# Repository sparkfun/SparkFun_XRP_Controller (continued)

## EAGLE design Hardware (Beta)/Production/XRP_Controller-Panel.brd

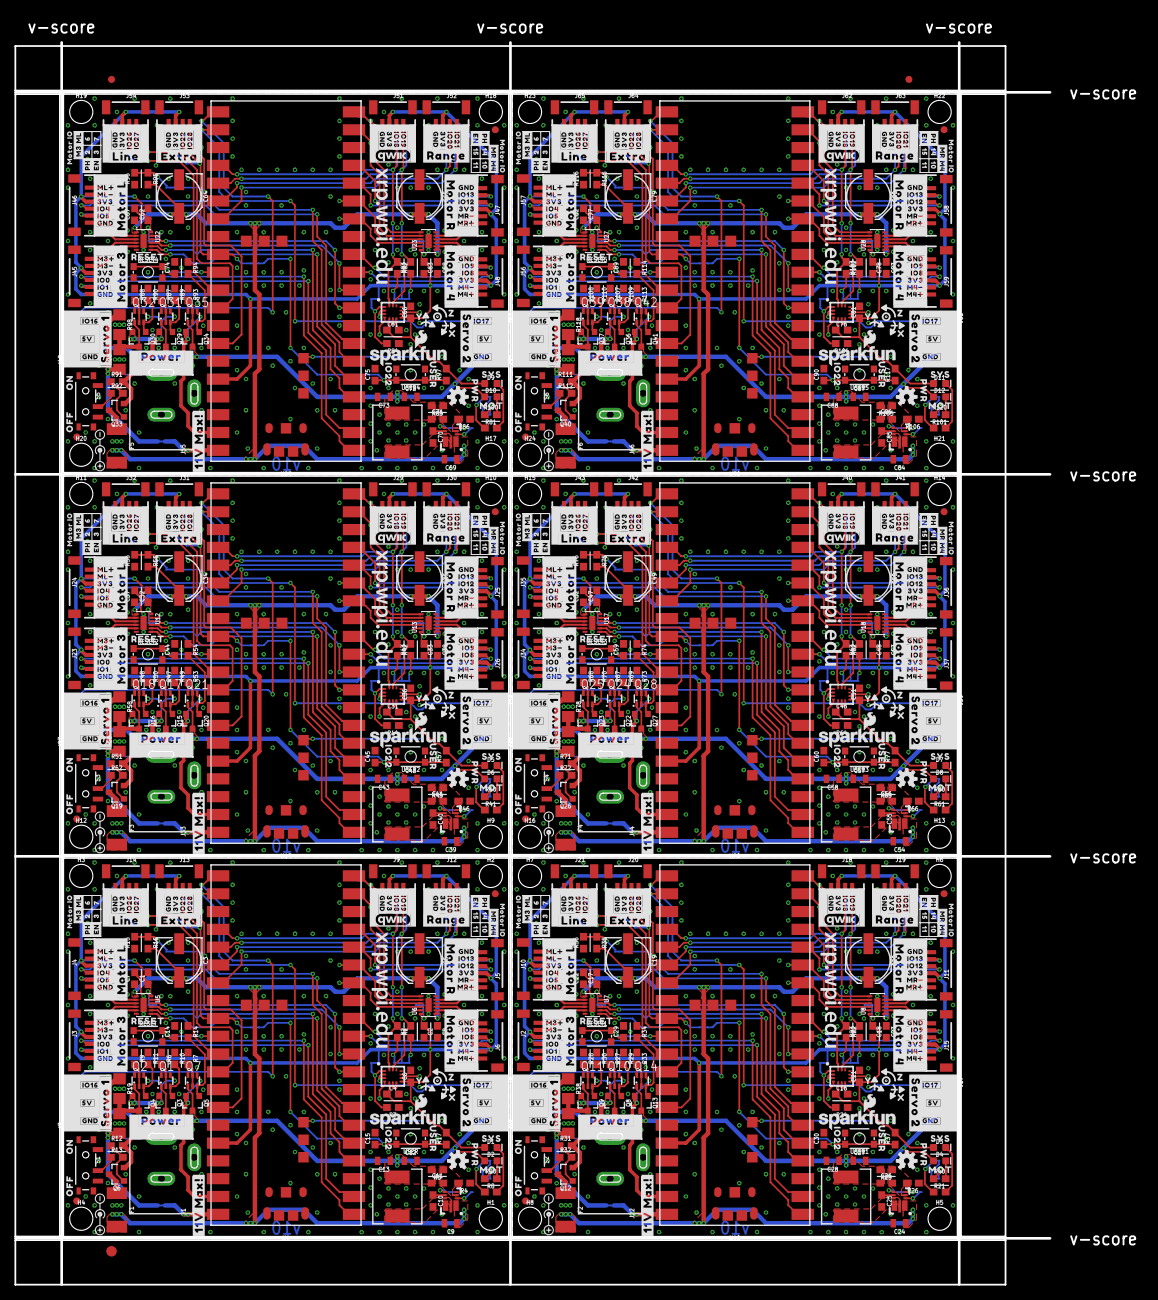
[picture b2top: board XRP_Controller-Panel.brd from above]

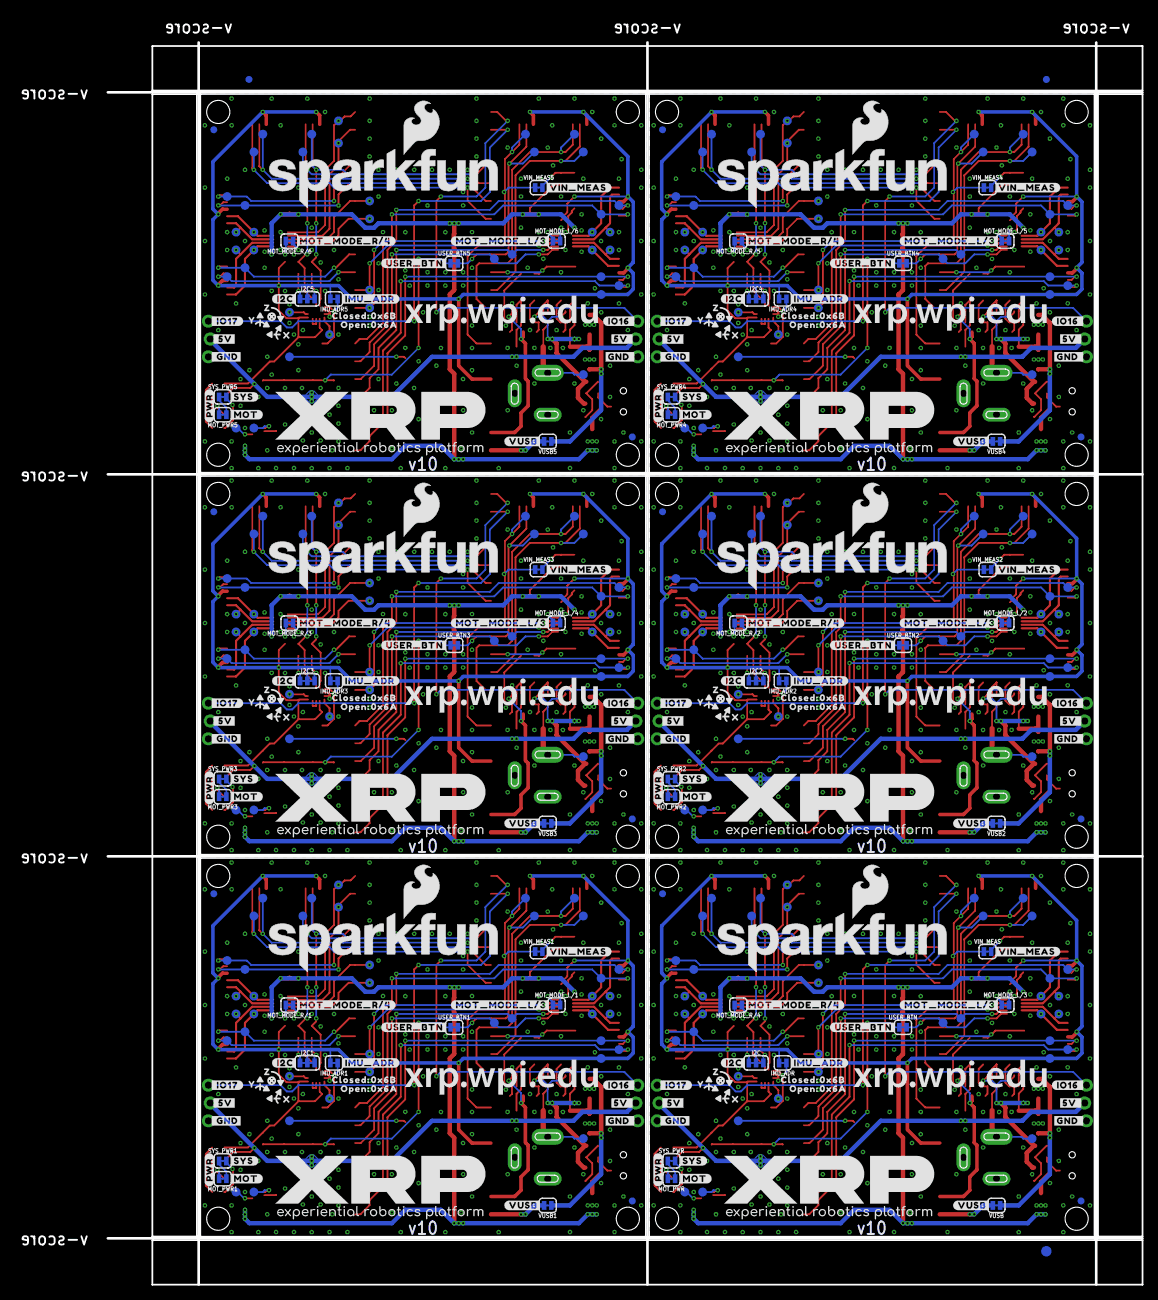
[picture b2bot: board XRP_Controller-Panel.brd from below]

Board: 2 copper layers, 147.6 x 177.2 mm, 1434 parts (459 on the bottom side), 438 nets.

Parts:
C1, C2, C4, C6, C7, C8, C10, C14, C15, C16, C17, C18, C21, C22, C23, C25, C29, C30, C31, C32, C33, C36, C37, C38, C40, C44, C45, C46, C47, C48, C51, C52, C53, C55, C59, C60, C61, C62, C63, C66, C67, C68, C70, C74, C75, C76, C77, C78, C81, C82, C83, C85, C89, C90: 0.1uF; 0603
C3, C5, C19, C20, C34, C35, C49, C50, C64, C65, C79, C80: 100uF; PANASONIC_D
C9, C24, C39, C54, C69, C84: 10uF; 0805
C11, C26, C41, C56, C71, C86: 47pF; 0603
C12, C13, C27, C28, C42, C43, C57, C58, C72, C73, C87, C88: 22uF; 0805
D1, D2, D3, D4, D5, D6, D7, D8, D9, D10, D11, D12: Red; LED-0603
E$1, E$2, E$3, E$4: FIDUCIAL-1X2
E$5, E$6: FIDUCIAL-1.5X3
F1, F2, F3, F4, F5, F6: 16V/2.5A(5A TRIP); 1812
FD1, FD2, FD3, FD4, FD5, FD6, FD7, FD8, FD9, FD10, FD11, FD12, FD13, FD14, FD15, FD16, FD17, FD18, FD19, FD20, FD21, FD22, FD23, FD24: FIDUCIAL1X2; FIDUCIAL-1X2
H1, H2, H3, H4, H5, H6, H7, H8, H9, H10, H11, H12, H13, H14, H15, H16, H17, H18, H19, H20, H21, H22, H23, H24: STAND-OFF
I2C, I2C1, I2C2, I2C3, I2C4, I2C5: JUMPER-SMT_3_2-NC_TRACE_SILK; SMT-JUMPER_3_2-NC_TRACE_SILK
IMU_ADR, IMU_ADR1, IMU_ADR2, IMU_ADR3, IMU_ADR4, IMU_ADR5: JUMPER-SMT_2_NC_TRACE_SILK; SMT-JUMPER_2_NC_TRACE_SILK
J1, J22, J33, J44, J55, J66: POWER_JACKPOWER_JACK_SLOT; POWER_JACK_PTH_SLOT
J2, J3, J4, J5, J6, J10, J11, J15, J23, J24, J25, J26, J34, J35, J36, J37, J45, J46, J47, J48, J56, J57, J58, J59: JST_6_PIN_VERTICAL; JST-6-SMD-VERT-1.0MM
J7, J8, J16, J17, J27, J28, J38, J39, J49, J50, J60, J61: 1X03_LOCK_NO_SILK
J9, J12, J13, J14, J18, J19, J20, J21, J29, J30, J31, J32, J40, J41, J42, J43, J51, J52, J53, J54, J62, J63, J64, J65: Vertical Qwiic Connector; JST04_1MM_VERT
L1, L2, L3, L4, L5, L6: 6.8UH; 07A7_6U8H
LOGO1, LOGO2, LOGO7, LOGO10, LOGO13, LOGO16: OSHW-LOGOS; OSHW-LOGO-S
LOGO3, LOGO5, LOGO8, LOGO11, LOGO14, LOGO17: SFE_LOGO_NAME_FLAME.3_INCH; SFE_LOGO_NAME_FLAME_.3
LOGO4, LOGO6, LOGO9, LOGO12, LOGO15, LOGO18: SFE_LOGO_NAME_FLAME.1_INCH; SFE_LOGO_NAME_FLAME_.1
MOT_MODE_L/1, MOT_MODE_L/2, MOT_MODE_L/3, MOT_MODE_L/4, MOT_MODE_L/5, MOT_MODE_L/6: JUMPER-SMT_2_NC_TRACE_SILK; SMT-JUMPER_2_NC_TRACE_SILK
MOT_MODE_R/1, MOT_MODE_R/2, MOT_MODE_R/3, MOT_MODE_R/4, MOT_MODE_R/5, MOT_MODE_R/6: JUMPER-SMT_2_NC_TRACE_SILK; SMT-JUMPER_2_NC_TRACE_SILK
MOT_PWR, MOT_PWR1, MOT_PWR2, MOT_PWR3, MOT_PWR4, MOT_PWR5: JUMPER-SMT_2_NC_TRACE_SILK; SMT-JUMPER_2_NC_TRACE_SILK
Q1, Q2, Q7, Q10, Q11, Q14, Q17, Q18, Q21, Q24, Q25, Q28, Q31, Q32, Q35, Q38, Q39, Q42: SOT363_PHILIPS
Q3, Q4, Q5, Q6, Q8, Q9, Q12, Q13, Q15, Q16, Q19, Q20, Q22, Q23, Q26, Q27, Q29, Q30, Q33, Q34, Q36, Q37, Q40, Q41: 20V/4.2A/52mΩ/1.4W; SOT23-3
R1, R2, R22, R23, R42, R43, R62, R63, R82, R83, R102, R103: 2.2k; 0603
R3, R6, R7, R9, R12, R13, R16, R17, R24, R27, R28, R31, R32, R33, R35, R37, R44, R47, R48, R51, R52, R53, R55, R57, R64, R67, R68, R71, R72, R73, R75, R77, R84, R87, R88, R91, R92, R93, R95, R97, R104, R107, R108, R111, R112, R113, R115, R117: 100k; 0603
R4, R15, R26, R36, R46, R56, R66, R76, R86, R96, R106, R116: 33k; 0603
R5, R25, R45, R65, R85, R105: 180k; 0603
R8, R21, R41, R61, R81, R101: 4.7k; 0603
R10, R11, R14, R29, R30, R34, R49, R50, R54, R69, R70, R74, R89, R90, R94, R109, R110, R114: 1M; 0603
R18, R19, R38, R39, R58, R59, R78, R79, R98, R99, R118, R119: 10; 1206
R20, R40, R60, R80, R100, R120: 10k; 0603
RESET, RESET1, RESET2, RESET3, RESET4, RESET5: MOMENTARY-SWITCH-SPST-SMD-4.6X2.8MM; TACTILE_SWITCH_SMD_4.6X2.8MM
S1, S2, S3, S4, S5, S6: SWITCH_SPST_SMD_A
SYS_PWR, SYS_PWR1, SYS_PWR2, SYS_PWR3, SYS_PWR4, SYS_PWR5: JUMPER-SMT_2_NC_TRACE_SILK; SMT-JUMPER_2_NC_TRACE_SILK
TP1, TP2, TP3, TP4, TP5, TP6, TP7, TP8, TP9, TP10, TP11, TP12, TP13, TP14, TP15, TP16, TP17, TP18, TP19, TP20, TP21, TP22, TP23, TP24, TP25, TP26, TP27, TP28, TP29, TP30, TP31, TP32, TP33, TP34, TP35, TP36, TP37, TP38, TP39, TP40, TP41, TP42, TP43, TP44, TP45, TP46, TP47, TP48, TP49, TP50, TP51, TP52, TP53, TP54, TP55, TP56, TP57, TP58, TP59, TP60, TP61, TP62, TP63, TP64, TP65, TP66, TP67, TP68, TP69, TP70, TP71, TP72, TP73, TP74, TP75, TP76, TP77, TP78, TP79, TP80, TP81, TP82, TP83, TP84, TP85, TP86, TP87, TP88, TP89, TP90, TP91, TP92, TP93, TP94, TP95, TP96, TP97, TP98, TP99, TP100, TP101, TP102, TP103, TP104, TP105, TP106, TP107, TP108, TP109, TP110, TP111, TP112, TP113, TP114, TP115, TP116, TP117, TP118, TP119, TP120, TP121, TP122, TP123, TP124, TP125, TP126, TP127, TP128, TP129, TP130, TP131, TP132, TP133, TP134, TP135, TP136, TP137, TP138, TP139, TP140, TP141, TP142, TP143, TP144, TP145, TP146, TP147, TP148, TP149, TP150, TP151, TP152, TP153, TP154, TP155, TP156, TP157, TP158, TP159, TP160, TP161, TP162, TP163, TP164, TP165, TP166, TP167, TP168, TP169, TP170, TP171, TP172, TP173, TP174, TP175, TP176, TP177, TP178, TP179, TP180, TP181, TP182, TP183, TP184, TP185, TP186, TP187, TP188, TP189, TP190, TP191, TP192, TP193, TP194, TP195, TP196, TP197, TP198, TP199, TP200, TP201, TP202, TP203, TP204, TP205, TP206, TP207, TP208, TP209, TP210, TP211, TP212, TP213, TP214, TP215, TP216, TP217, TP218, TP219, TP220, TP221, TP222, TP223, TP224, TP225, TP226, TP227, TP228, TP229, TP230, TP231, TP232, TP233, TP234: TEST-POINT3X5; PAD.03X.05
U1, U10, U15, U20, U25, U30: RPI_PICO_W_XRP; RPI_PICO_W
U2, U9, U14, U19, U24, U29: AP63357; V-DFN3020-13
U3, U4, U11, U16, U21, U26: LSM6DS0X; LGA14L
U5, U6, U7, U8, U12, U13, U17, U18, U22, U23, U27, U28: DRV8835; WSON-12
U$1, U$165, U$279, U$393, U$507, U$621: #MOTOR_3#0
U$2, U$169, U$283, U$397, U$511, U$625: #SERVO_2#0
U$3, U$170, U$284, U$398, U$512, U$626: #11V_MAX###0
U$4, U$24, U$50, U$52, U$54, U$118, U$124, U$146, U$148, U$150, U$232, U$238, U$260, U$262, U$264, U$346, U$352, U$374, U$376, U$378, U$460, U$466, U$488, U$490, U$492, U$574, U$580, U$602, U$604, U$606: #GND#0
U$5, U$36, U$229, U$343, U$457, U$571: #POWER#0
U$6, U$112, U$230, U$344, U$458, U$572: PWR0
U$7, U$113, U$231, U$345, U$459, U$573: RESET0
U$8, U$167, U$281, U$395, U$509, U$623: #MOTOR_R#0
U$9, U$207, U$321, U$435, U$549, U$663: #MR##0
U$10, U$164, U$278, U$392, U$506, U$620: #MOTOR_L#0
U$11, U$166, U$280, U$394, U$508, U$622: #SERVO_1#0
U$12, U$168, U$282, U$396, U$510, U$624: #MOTOR_4#0
U$13, U$182, U$296, U$410, U$524, U$638: #VIN_MEAS#0
U$14, U$208, U$322, U$436, U$550, U$664: #MR##1
U$15, U$25, U$51, U$53, U$119, U$125, U$147, U$149, U$233, U$239, U$261, U$263, U$347, U$353, U$375, U$377, U$461, U$467, U$489, U$491, U$575, U$581, U$603, U$605: #3V3#0
U$16, U$205, U$319, U$433, U$547, U$661: #ML##0
U$17, U$33, U$41, U$43, U$129, U$131, U$137, U$139, U$243, U$245, U$251, U$253, U$357, U$359, U$365, U$367, U$471, U$473, U$479, U$481, U$585, U$587, U$593, U$595: #3V3#4
U$18, U$209, U$323, U$437, U$551, U$665: #M4##0
U$19, U$210, U$324, U$438, U$552, U$666: #M4##5
U$20, U$120, U$234, U$348, U$462, U$576: #IO0#0
U$21, U$121, U$235, U$349, U$463, U$577: #IO1#0
U$22, U$122, U$236, U$350, U$464, U$578: #IO5#0
U$23, U$123, U$237, U$351, U$465, U$579: #IO4#0
U$26, U$172, U$286, U$400, U$514, U$628: #GND_#0
U$27, U$171, U$285, U$399, U$513, U$627: #5V_#0
U$28, U$126, U$240, U$354, U$468, U$582: #IO8#0
U$29, U$127, U$241, U$355, U$469, U$583: #IO9#0
U$30, U$31, U$40, U$42, U$57, U$128, U$130, U$136, U$138, U$153, U$242, U$244, U$250, U$252, U$267, U$356, U$358, U$364, U$366, U$381, U$470, U$472, U$478, U$480, U$495, U$584, U$586, U$592, U$594, U$609: #GND#10
U$32, U$206, U$320, U$434, U$548, U$662: #ML##1
U$34, U$132, U$246, U$360, U$474, U$588: #IO12#0
U$35, U$133, U$247, U$361, U$475, U$589: #IO13#0
U$37, U$117, U$218, U$222, U$332, U$336, U$446, U$450, U$560, U$564, U$674, U$678: #PH#0
U$38, U$134, U$248, U$362, U$476, U$590: #IO27#0
U$39, U$135, U$249, U$363, U$477, U$591: #IO28#0
U$44, U$140, U$254, U$368, U$482, U$596: #IO26#0
U$45, U$141, U$255, U$369, U$483, U$597: #IO22#0
U$46, U$142, U$256, U$370, U$484, U$598: #IO18#0
U$47, U$143, U$257, U$371, U$485, U$599: #IO19#0
U$48, U$144, U$258, U$372, U$486, U$600: #IO20#0
U$49, U$145, U$259, U$373, U$487, U$601: #IO21#0
U$55, U$151, U$265, U$379, U$493, U$607: #5V#0
U$56, U$152, U$266, U$380, U$494, U$608: #IO16#0
U$58, U$154, U$268, U$382, U$496, U$610: #IO17#0
U$59, U$155, U$269, U$383, U$497, U$611: #5V#18
U$60, U$156, U$270, U$384, U$498, U$612: #I2C#0
U$61, U$173, U$287, U$401, U$515, U$629: #IO16_#0
U$62, U$157, U$271, U$385, U$499, U$613: ON0
U$63, U$158, U$272, U$386, U$500, U$614: OFF0
U$64, U$162, U$276, U$390, U$504, U$618: #IMU_ADR#0
U$65, U$116, U$217, U$221, U$331, U$335, U$445, U$449, U$559, U$563, U$673, U$677: #EN#0
U$66, U$194, U$308, U$422, U$536, U$650: #MOT_MODE_L#3#0
U$67, U$195, U$309, U$423, U$537, U$651: SYS0
U$68, U$191, U$305, U$419, U$533, U$647: IO220
U$69, U$192, U$306, U$420, U$534, U$648: #RANGE#0
U$70, U$193, U$307, U$421, U$535, U$649: #MOT_MODE_R#4#0
U$71, U$196, U$310, U$424, U$538, U$652: MOT0
U$72, U$201, U$315, U$429, U$543, U$657: XRP_URL_3MM
U$73, U$199, U$313, U$427, U$541, U$655: #PWR#0
U$74, U$163, U$277, U$391, U$505, U$619: #LINE#0
U$75, U$174, U$288, U$402, U$516, U$630: #_GND#0
U$76, U$175, U$289, U$403, U$517, U$631: #_5V#0
U$77, U$176, U$290, U$404, U$518, U$632: #_IO17#0
U$78, U$177, U$291, U$405, U$519, U$633: POLARITY_MARKING_CENTER_POSITIVE#JPG
U$79, U$88, U$159, U$178, U$273, U$292, U$387, U$406, U$501, U$520, U$615, U$634: X0
U$80, U$89, U$160, U$179, U$274, U$293, U$388, U$407, U$502, U$521, U$616, U$635: Y0
U$81, U$90, U$161, U$180, U$275, U$294, U$389, U$408, U$503, U$522, U$617, U$636: Z0
U$82, U$181, U$295, U$409, U$523, U$637: #EXTRA#0
U$83, U$183, U$297, U$411, U$525, U$639: USER0
U$84, U$184, U$298, U$412, U$526, U$640: #USER_BTN#0
U$85, U$185, U$299, U$413, U$527, U$641: 0X6B0
U$86, U$186, U$300, U$414, U$528, U$642: 0X6A0
U$87, U$187, U$301, U$415, U$529, U$643: OPEN#0
U$91, U$188, U$302, U$416, U$530, U$644: CLOSED#0
U$92, U$189, U$303, U$417, U$531, U$645: XRP_FULL_LOGO
U$93, U$190, U$304, U$418, U$532, U$646: #VUSB#0
U$94, U$203, U$317, U$431, U$545, U$659: #M3##0
U$95, U$197, U$311, U$425, U$539, U$653: #MOT#0
U$96, U$198, U$312, U$426, U$540, U$654: #SYS#0
U$97, U$202, U$316, U$430, U$544, U$658: XRP_URL_5MM
U$98, U$200, U$314, U$428, U$542, U$656: QWIIC_LOGO; QWIIC_INVERTED
U$99, U$204, U$318, U$432, U$546, U$660: #M3##4
U$100, U$219, U$333, U$447, U$561, U$675: #ML#0
U$101, U$220, U$334, U$448, U$562, U$676: #M3#0
U$102, U$211, U$325, U$439, U$553, U$667: 100
U$103, U$212, U$326, U$440, U$554, U$668: 110
U$104, U$213, U$327, U$441, U$555, U$669: 140
U$105, U$214, U$328, U$442, U$556, U$670: 150
U$106, U$224, U$338, U$452, U$566, U$680: #MR#0
U$107, U$223, U$337, U$451, U$565, U$679: #M4#0
U$108, U$225, U$339, U$453, U$567, U$681: 20
U$109, U$226, U$340, U$454, U$568, U$682: 30
U$110, U$227, U$341, U$455, U$569, U$683: 60
U$111, U$228, U$342, U$456, U$570, U$684: 70
U$114, U$115, U$215, U$216, U$329, U$330, U$443, U$444, U$557, U$558, U$671, U$672: MOTOR_IO0
USER, USER1, USER2, USER3, USER4, USER5: MOMENTARY-SWITCH-SPST-SMD-4.6X2.8MM; TACTILE_SWITCH_SMD_4.6X2.8MM
USER_BTN, USER_BTN1, USER_BTN2, USER_BTN3, USER_BTN4, USER_BTN5: JUMPER-SMT_2_NC_TRACE_SILK; SMT-JUMPER_2_NC_TRACE_SILK
VIN_MEAS, VIN_MEAS1, VIN_MEAS2, VIN_MEAS3, VIN_MEAS4, VIN_MEAS5: JUMPER-SMT_2_NC_TRACE_SILK; SMT-JUMPER_2_NC_TRACE_SILK
VUSB, VUSB1, VUSB2, VUSB3, VUSB4, VUSB5: JUMPER-SMT_2_NC_TRACE_SILK; SMT-JUMPER_2_NC_TRACE_SILK

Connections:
3.3V: C1.1, C2.1, C4.1, C6.1, D1.A, I2C.2, IMU_ADR.2, J3.3, J4.3, J5.3, J6.3, J9.2, J12.2, J13.2, J14.2, MOT_MODE_L/3.2, MOT_MODE_R/4.2, R17.2, TP33.1, U1.36, U4.5, U4.8, U5.12, U6.12
3.3V1: C16.1, C17.1, C18.1, C21.1, D3.A, I2C1.2, IMU_ADR1.2, J2.3, J10.3, J11.3, J15.3, J18.2, J19.2, J20.2, J21.2, MOT_MODE_L/1.2, MOT_MODE_R/1.2, R37.2, TP72.1, U3.5, U3.8, U7.12, U8.12, U10.36
3.3V2: C31.1, C32.1, C33.1, C36.1, D5.A, I2C2.2, IMU_ADR2.2, J23.3, J24.3, J25.3, J26.3, J29.2, J30.2, J31.2, J32.2, MOT_MODE_L/2.2, MOT_MODE_R/2.2, R57.2, TP111.1, U11.5, U11.8, U12.12, U13.12, U15.36
3.3V3: C46.1, C47.1, C48.1, C51.1, D7.A, I2C3.2, IMU_ADR3.2, J34.3, J35.3, J36.3, J37.3, J40.2, J41.2, J42.2, J43.2, MOT_MODE_L/4.2, MOT_MODE_R/3.2, R77.2, TP150.1, U16.5, U16.8, U17.12, U18.12, U20.36
3.3V4: C61.1, C62.1, C63.1, C66.1, D9.A, I2C4.2, IMU_ADR4.2, J45.3, J46.3, J47.3, J48.3, J51.2, J52.2, J53.2, J54.2, MOT_MODE_L/5.2, MOT_MODE_R/5.2, R97.2, TP189.1, U21.5, U21.8, U22.12, U23.12, U25.36
3.3V5: C76.1, C77.1, C78.1, C81.1, D11.A, I2C5.2, IMU_ADR5.2, J56.3, J57.3, J58.3, J59.3, J62.2, J63.2, J64.2, J65.2, MOT_MODE_L/6.2, MOT_MODE_R/6.2, R117.2, TP228.1, U26.5, U26.8, U27.12, U28.12, U30.36
5V: C11.1, C12.1, C13.1, D2.A, J7.2, J8.2, L1.P$2, Q5.3, Q7.1, R5.2
5V1: C26.1, C27.1, C28.1, D4.A, J16.2, J17.2, L2.P$2, Q13.3, Q14.1, R25.2
5V2: C41.1, C42.1, C43.1, D6.A, J27.2, J28.2, L3.P$2, Q20.3, Q21.1, R45.2
5V3: C56.1, C57.1, C58.1, D8.A, J38.2, J39.2, L4.P$2, Q27.3, Q28.1, R65.2
5V4: C71.1, C72.1, C73.1, D10.A, J49.2, J50.2, L5.P$2, Q34.3, Q35.1, R85.2
5V5: C86.1, C87.1, C88.1, D12.A, J60.2, J61.2, L6.P$2, Q41.3, Q42.1, R105.2
5V_EN: TP35.1, U2.P$2
5V_EN1: TP73.1, U9.P$2
5V_EN2: TP112.1, U14.P$2
5V_EN3: TP151.1, U19.P$2
5V_EN4: TP190.1, U24.P$2
5V_EN5: TP229.1, U29.P$2
5V_PG: TP36.1, U2.P$5
5V_PG1: TP74.1, U9.P$5
5V_PG2: TP113.1, U14.P$5
5V_PG3: TP152.1, U19.P$5
5V_PG4: TP191.1, U24.P$5
5V_PG5: TP230.1, U29.P$5
!POW_EN!: R13.1, S1.2
!POW_EN!1: R32.1, S2.2
!POW_EN!2: R52.1, S3.2
!POW_EN!3: R72.1, S4.2
!POW_EN!4: R92.1, S5.2
!POW_EN!5: R112.1, S6.2
!RP_RESET!: C14.1, RESET.3, RESET.4, U1.30
!RP_RESET!1: C29.1, RESET1.3, RESET1.4, U10.30
!RP_RESET!2: C44.1, RESET2.3, RESET2.4, U15.30
!RP_RESET!3: C59.1, RESET3.3, RESET3.4, U20.30
!RP_RESET!4: C74.1, RESET4.3, RESET4.4, U25.30
!RP_RESET!5: C89.1, RESET5.3, RESET5.4, U30.30
BOOTSEL: TP37.1, U1.46
BOOTSEL1: TP75.1, U10.46
BOOTSEL2: TP114.1, U15.46
BOOTSEL3: TP153.1, U20.46
BOOTSEL4: TP192.1, U25.46
BOOTSEL5: TP231.1, U30.46
FB: C11.2, R4.2, R5.1, U2.P$3
FB1: C26.2, R25.1, R26.2, U9.P$3
FB2: C41.2, R45.1, R46.2, U14.P$3
FB3: C56.2, R65.1, R66.2, U19.P$3
FB4: C71.2, R85.1, R86.2, U24.P$3
FB5: C86.2, R105.1, R106.2, U29.P$3
GND: C1.2, C2.2, C3.-, C4.2, C5.-, C6.2, C7.2, C8.2, C9.2, C12.2, C13.2, C14.2, C15.2, J1.GND, J3.6, J4.6, J5.6, J6.6, J7.1, J8.3, J9.1, J12.1, J13.1, J14.1, MOT_PWR.1, R3.1, R4.1, R6.1, R7.1, R9.1, R10.1, R11.1, R14.1, R15.1, RESET.1, RESET.2, S1.3, SYS_PWR.1, U1.3, U1.8, U1.13, U1.18, U1.23, U1.28, U1.33, U1.38, U1.41, U1.48, U1.A, U1.B, U1.C, U1.D, U2.P$4, U2.P$8, U4.2, U4.3, U4.6, U4.7, U5.6, U5.PAD, U6.6, U6.PAD, USER.1, USER.2
GND1: C16.2, C17.2, C18.2, C19.-, C20.-, C21.2, C22.2, C23.2, C24.2, C27.2, C28.2, C29.2, C30.2, J2.6, J10.6, J11.6, J15.6, J16.1, J17.3, J18.1, J19.1, J20.1, J21.1, J22.GND, MOT_PWR1.1, R24.1, R26.1, R27.1, R28.1, R29.1, R30.1, R33.1, R34.1, R36.1, RESET1.1, RESET1.2, S2.3, SYS_PWR1.1, U3.2, U3.3, U3.6, U3.7, U7.6, U7.PAD, U8.6, U8.PAD, U9.P$4, U9.P$8, U10.3, U10.8, U10.13, U10.18, U10.23, U10.28, U10.33, U10.38, U10.41, U10.48, U10.A, U10.B, U10.C, U10.D, USER1.1, USER1.2
GND2: C31.2, C32.2, C33.2, C34.-, C35.-, C36.2, C37.2, C38.2, C39.2, C42.2, C43.2, C44.2, C45.2, J23.6, J24.6, J25.6, J26.6, J27.1, J28.3, J29.1, J30.1, J31.1, J32.1, J33.GND, MOT_PWR2.1, R44.1, R46.1, R47.1, R48.1, R49.1, R50.1, R53.1, R54.1, R56.1, RESET2.1, RESET2.2, S3.3, SYS_PWR2.1, U11.2, U11.3, U11.6, U11.7, U12.6, U12.PAD, U13.6, U13.PAD, U14.P$4, U14.P$8, U15.3, U15.8, U15.13, U15.18, U15.23, U15.28, U15.33, U15.38, U15.41, U15.48, U15.A, U15.B, U15.C, U15.D, USER2.1, USER2.2
GND3: C46.2, C47.2, C48.2, C49.-, C50.-, C51.2, C52.2, C53.2, C54.2, C57.2, C58.2, C59.2, C60.2, J34.6, J35.6, J36.6, J37.6, J38.1, J39.3, J40.1, J41.1, J42.1, J43.1, J44.GND, MOT_PWR3.1, R64.1, R66.1, R67.1, R68.1, R69.1, R70.1, R73.1, R74.1, R76.1, RESET3.1, RESET3.2, S4.3, SYS_PWR3.1, U16.2, U16.3, U16.6, U16.7, U17.6, U17.PAD, U18.6, U18.PAD, U19.P$4, U19.P$8, U20.3, U20.8, U20.13, U20.18, U20.23, U20.28, U20.33, U20.38, U20.41, U20.48, U20.A, U20.B, U20.C, U20.D, USER3.1, USER3.2
GND4: C61.2, C62.2, C63.2, C64.-, C65.-, C66.2, C67.2, C68.2, C69.2, C72.2, C73.2, C74.2, C75.2, J45.6, J46.6, J47.6, J48.6, J49.1, J50.3, J51.1, J52.1, J53.1, J54.1, J55.GND, MOT_PWR4.1, R84.1, R86.1, R87.1, R88.1, R89.1, R90.1, R93.1, R94.1, R96.1, RESET4.1, RESET4.2, S5.3, SYS_PWR4.1, U21.2, U21.3, U21.6, U21.7, U22.6, U22.PAD, U23.6, U23.PAD, U24.P$4, U24.P$8, U25.3, U25.8, U25.13, U25.18, U25.23, U25.28, U25.33, U25.38, U25.41, U25.48, U25.A, U25.B, U25.C, U25.D, USER4.1, USER4.2
GND5: C76.2, C77.2, C78.2, C79.-, C80.-, C81.2, C82.2, C83.2, C84.2, C87.2, C88.2, C89.2, C90.2, J56.6, J57.6, J58.6, J59.6, J60.1, J61.3, J62.1, J63.1, J64.1, J65.1, J66.GND, MOT_PWR5.1, R104.1, R106.1, R107.1, R108.1, R109.1, R110.1, R113.1, R114.1, R116.1, RESET5.1, RESET5.2, S6.3, SYS_PWR5.1, U26.2, U26.3, U26.6, U26.7, U27.6, U27.PAD, U28.6, U28.PAD, U29.P$4, U29.P$8, U30.3, U30.8, U30.13, U30.18, U30.23, U30.28, U30.33, U30.38, U30.41, U30.48, U30.A, U30.B, U30.C, U30.D, USER5.1, USER5.2
IMU_INT1: TP38.1, U4.4
IMU_INT2: TP39.1, U4.9
IMU_INT3: TP77.1, U3.9
IMU_INT4: TP78.1, U3.4
IMU_INT5: TP116.1, U11.9
IMU_INT6: TP117.1, U11.4
IMU_INT7: TP155.1, U16.9
IMU_INT8: TP156.1, U16.4
IMU_INT9: TP194.1, U21.9
IMU_INT10: TP195.1, U21.4
IMU_INT11: TP233.1, U26.9
IMU_INT12: TP234.1, U26.4
MOT_3+: J3.1, TP25.1, U5.4
MOT_3+1: J2.1, TP64.1, U7.4
MOT_3+2: J23.1, TP103.1, U12.4
MOT_3+3: J34.1, TP142.1, U17.4
MOT_3+4: J45.1, TP181.1, U22.4
MOT_3+5: J56.1, TP220.1, U27.4
MOT_3-: J3.2, TP26.1, U5.5
MOT_3-1: J2.2, TP65.1, U7.5
MOT_3-2: J23.2, TP104.1, U12.5
MOT_3-3: J34.2, TP143.1, U17.5
MOT_3-4: J45.2, TP182.1, U22.5
MOT_3-5: J56.2, TP221.1, U27.5
MOT_4+: J6.1, TP29.1, U6.2
MOT_4+1: J15.1, TP68.1, U8.2
MOT_4+2: J26.1, TP107.1, U13.2
MOT_4+3: J37.1, TP146.1, U18.2
MOT_4+4: J48.1, TP185.1, U23.2
MOT_4+5: J59.1, TP224.1, U28.2
MOT_4-: J6.2, TP31.1, U6.3
MOT_4-1: J15.2, TP70.1, U8.3
MOT_4-2: J26.2, TP109.1, U13.3
MOT_4-3: J37.2, TP148.1, U18.3
MOT_4-4: J48.2, TP187.1, U23.3
MOT_4-5: J59.2, TP226.1, U28.3
MOT_L+: J4.1, TP27.1, U5.2
MOT_L+1: J10.1, TP66.1, U7.2
MOT_L+2: J24.1, TP105.1, U12.2
MOT_L+3: J35.1, TP144.1, U17.2
MOT_L+4: J46.1, TP183.1, U22.2
MOT_L+5: J57.1, TP222.1, U27.2
MOT_L-: J4.2, TP28.1, U5.3
MOT_L-1: J10.2, TP67.1, U7.3
MOT_L-2: J24.2, TP106.1, U12.3
MOT_L-3: J35.2, TP145.1, U17.3
MOT_L-4: J46.2, TP184.1, U22.3
MOT_L-5: J57.2, TP223.1, U27.3
MOT_R+: J5.1, TP30.1, U6.4
MOT_R+1: J11.1, TP69.1, U8.4
MOT_R+2: J25.1, TP108.1, U13.4
MOT_R+3: J36.1, TP147.1, U18.4
MOT_R+4: J47.1, TP186.1, U23.4
MOT_R+5: J58.1, TP225.1, U28.4
MOT_R-: J5.2, TP32.1, U6.5
MOT_R-1: J11.2, TP71.1, U8.5
MOT_R-2: J25.2, TP110.1, U13.5
MOT_R-3: J36.2, TP149.1, U18.5
MOT_R-4: J47.2, TP188.1, U23.5
MOT_R-5: J58.2, TP227.1, U28.5
unnamed: D1.C, R8.2
unnamed: IMU_ADR.1, R3.2, U4.1
unnamed: I2C.3, R1.2
unnamed: I2C.1, R2.1
unnamed: C10.1, U2.P$6
unnamed: Q1.2, Q1.5, Q1.6, R6.2
unnamed: Q1.3, Q3.1, R10.2
unnamed: F1.1, Q6.3
unnamed: U1.40, VUSB.2
unnamed: R8.1, SYS_PWR.2
unnamed: Q2.2, Q2.5, Q2.6, R9.2
unnamed: R15.2, R16.1, VIN_MEAS.2
unnamed: MOT_MODE_L/3.1, U5.11
unnamed: MOT_MODE_R/4.1, U6.11
unnamed: Q6.1, R12.1, R13.2
unnamed: Q2.3, Q4.1, R11.2
unnamed: C15.1, R17.1, USER.3, USER.4, USER_BTN.1
unnamed: R18.1, R19.1, VUSB.1
unnamed: Q7.2, Q7.5, Q7.6, R7.2
unnamed: Q5.1, Q7.3, R14.2
unnamed: D2.C, R20.2
unnamed: MOT_PWR.2, R20.1
unnamed: D3.C, R21.2
unnamed: R21.1, SYS_PWR1.2
unnamed: MOT_MODE_L/1.1, U7.11
unnamed: MOT_MODE_R/1.1, U8.11
unnamed: IMU_ADR1.1, R24.2, U3.1
unnamed: I2C1.3, R22.2
unnamed: I2C1.1, R23.1
unnamed: C25.1, U9.P$6
unnamed: Q10.2, Q10.5, Q10.6, R27.2
unnamed: Q8.1, Q10.3, R29.2
unnamed: Q11.2, Q11.5, Q11.6, R28.2
unnamed: Q9.1, Q11.3, R30.2
unnamed: Q12.1, R31.1, R32.2
unnamed: F2.1, Q12.3
unnamed: Q14.2, Q14.5, Q14.6, R33.2
unnamed: Q13.1, Q14.3, R34.2
unnamed: R35.1, R36.2, VIN_MEAS1.2
unnamed: C30.1, R37.1, USER1.3, USER1.4, USER_BTN1.1
unnamed: U10.40, VUSB1.2
unnamed: R38.1, R39.1, VUSB1.1
unnamed: D4.C, R40.2
unnamed: MOT_PWR1.2, R40.1
unnamed: D5.C, R41.2
unnamed: R41.1, SYS_PWR2.2
unnamed: MOT_MODE_L/2.1, U12.11
unnamed: MOT_MODE_R/2.1, U13.11
unnamed: IMU_ADR2.1, R44.2, U11.1
unnamed: I2C2.3, R42.2
unnamed: I2C2.1, R43.1
unnamed: C40.1, U14.P$6
unnamed: Q17.2, Q17.5, Q17.6, R47.2
unnamed: Q15.1, Q17.3, R49.2
unnamed: Q18.2, Q18.5, Q18.6, R48.2
unnamed: Q16.1, Q18.3, R50.2
unnamed: Q19.1, R51.1, R52.2
unnamed: F3.1, Q19.3
unnamed: Q21.2, Q21.5, Q21.6, R53.2
unnamed: Q20.1, Q21.3, R54.2
unnamed: R55.1, R56.2, VIN_MEAS2.2
unnamed: C45.1, R57.1, USER2.3, USER2.4, USER_BTN2.1
unnamed: U15.40, VUSB2.2
unnamed: R58.1, R59.1, VUSB2.1
unnamed: D6.C, R60.2
unnamed: MOT_PWR2.2, R60.1
unnamed: D7.C, R61.2
unnamed: R61.1, SYS_PWR3.2
unnamed: MOT_MODE_L/4.1, U17.11
unnamed: MOT_MODE_R/3.1, U18.11
unnamed: IMU_ADR3.1, R64.2, U16.1
unnamed: I2C3.3, R62.2
unnamed: I2C3.1, R63.1
unnamed: C55.1, U19.P$6
unnamed: Q24.2, Q24.5, Q24.6, R67.2
unnamed: Q22.1, Q24.3, R69.2
unnamed: Q25.2, Q25.5, Q25.6, R68.2
unnamed: Q23.1, Q25.3, R70.2
unnamed: Q26.1, R71.1, R72.2
unnamed: F4.1, Q26.3
unnamed: Q28.2, Q28.5, Q28.6, R73.2
unnamed: Q27.1, Q28.3, R74.2
unnamed: R75.1, R76.2, VIN_MEAS3.2
unnamed: C60.1, R77.1, USER3.3, USER3.4, USER_BTN3.1
unnamed: U20.40, VUSB3.2
unnamed: R78.1, R79.1, VUSB3.1
unnamed: D8.C, R80.2
unnamed: MOT_PWR3.2, R80.1
unnamed: D9.C, R81.2
unnamed: R81.1, SYS_PWR4.2
unnamed: MOT_MODE_L/5.1, U22.11
unnamed: MOT_MODE_R/5.1, U23.11
unnamed: IMU_ADR4.1, R84.2, U21.1
unnamed: I2C4.3, R82.2
unnamed: I2C4.1, R83.1
unnamed: C70.1, U24.P$6
unnamed: Q31.2, Q31.5, Q31.6, R87.2
unnamed: Q29.1, Q31.3, R89.2
unnamed: Q32.2, Q32.5, Q32.6, R88.2
unnamed: Q30.1, Q32.3, R90.2
unnamed: Q33.1, R91.1, R92.2
unnamed: F5.1, Q33.3
unnamed: Q35.2, Q35.5, Q35.6, R93.2
unnamed: Q34.1, Q35.3, R94.2
unnamed: R95.1, R96.2, VIN_MEAS4.2
unnamed: C75.1, R97.1, USER4.3, USER4.4, USER_BTN4.1
unnamed: U25.40, VUSB4.2
unnamed: R98.1, R99.1, VUSB4.1
unnamed: D10.C, R100.2
unnamed: MOT_PWR4.2, R100.1
unnamed: D11.C, R101.2
unnamed: R101.1, SYS_PWR5.2
unnamed: MOT_MODE_L/6.1, U27.11
unnamed: MOT_MODE_R/6.1, U28.11
unnamed: IMU_ADR5.1, R104.2, U26.1
unnamed: I2C5.3, R102.2
unnamed: I2C5.1, R103.1
unnamed: C85.1, U29.P$6
unnamed: Q38.2, Q38.5, Q38.6, R107.2
unnamed: Q36.1, Q38.3, R109.2
unnamed: Q39.2, Q39.5, Q39.6, R108.2
unnamed: Q37.1, Q39.3, R110.2
unnamed: Q40.1, R111.1, R112.2
unnamed: F6.1, Q40.3
unnamed: Q42.2, Q42.5, Q42.6, R113.2
unnamed: Q41.1, Q42.3, R114.2
unnamed: R115.1, R116.2, VIN_MEAS5.2
unnamed: C90.1, R117.1, USER5.3, USER5.4, USER_BTN5.1
unnamed: U30.40, VUSB5.2
unnamed: R118.1, R119.1, VUSB5.1
unnamed: D12.C, R120.2
unnamed: MOT_PWR5.2, R120.1
RP_IO0/ENC_3_A: J3.4, TP1.1, U1.1
RP_IO0/ENC_3_A1: J2.4, TP40.1, U10.1
RP_IO0/ENC_3_A2: J23.4, TP79.1, U15.1
RP_IO0/ENC_3_A3: J34.4, TP118.1, U20.1
RP_IO0/ENC_3_A4: J45.4, TP157.1, U25.1
RP_IO0/ENC_3_A5: J56.4, TP196.1, U30.1
RP_IO1/ENC_3_B: J3.5, TP2.1, U1.2
RP_IO1/ENC_3_B1: J2.5, TP41.1, U10.2
RP_IO1/ENC_3_B2: J23.5, TP80.1, U15.2
RP_IO1/ENC_3_B3: J34.5, TP119.1, U20.2
RP_IO1/ENC_3_B4: J45.5, TP158.1, U25.2
RP_IO1/ENC_3_B5: J56.5, TP197.1, U30.2
RP_IO2/MOT_3_PH: TP3.1, U1.4, U5.8
RP_IO2/MOT_3_PH1: TP42.1, U7.8, U10.4
RP_IO2/MOT_3_PH2: TP81.1, U12.8, U15.4
RP_IO2/MOT_3_PH3: TP120.1, U17.8, U20.4
RP_IO2/MOT_3_PH4: TP159.1, U22.8, U25.4
RP_IO2/MOT_3_PH5: TP198.1, U27.8, U30.4
RP_IO3/MOT_3_EN: TP4.1, U1.5, U5.7
RP_IO3/MOT_3_EN1: TP43.1, U7.7, U10.5
RP_IO3/MOT_3_EN2: TP82.1, U12.7, U15.5
RP_IO3/MOT_3_EN3: TP121.1, U17.7, U20.5
RP_IO3/MOT_3_EN4: TP160.1, U22.7, U25.5
RP_IO3/MOT_3_EN5: TP199.1, U27.7, U30.5
RP_IO4/ENC_L_A: J4.4, TP5.1, U1.6
RP_IO4/ENC_L_A1: J10.4, TP44.1, U10.6
RP_IO4/ENC_L_A2: J24.4, TP83.1, U15.6
RP_IO4/ENC_L_A3: J35.4, TP122.1, U20.6
RP_IO4/ENC_L_A4: J46.4, TP161.1, U25.6
RP_IO4/ENC_L_A5: J57.4, TP200.1, U30.6
RP_IO5/ENC_L_B: J4.5, TP6.1, U1.7
RP_IO5/ENC_L_B1: J10.5, TP45.1, U10.7
RP_IO5/ENC_L_B2: J24.5, TP84.1, U15.7
RP_IO5/ENC_L_B3: J35.5, TP123.1, U20.7
RP_IO5/ENC_L_B4: J46.5, TP162.1, U25.7
RP_IO5/ENC_L_B5: J57.5, TP201.1, U30.7
RP_IO6/MOT_L_PH: TP7.1, U1.9, U5.10
RP_IO6/MOT_L_PH1: TP46.1, U7.10, U10.9
RP_IO6/MOT_L_PH2: TP85.1, U12.10, U15.9
RP_IO6/MOT_L_PH3: TP124.1, U17.10, U20.9
RP_IO6/MOT_L_PH4: TP163.1, U22.10, U25.9
RP_IO6/MOT_L_PH5: TP202.1, U27.10, U30.9
RP_IO7/MOT_L_EN: TP8.1, U1.10, U5.9
RP_IO7/MOT_L_EN1: TP47.1, U7.9, U10.10
RP_IO7/MOT_L_EN2: TP86.1, U12.9, U15.10
RP_IO7/MOT_L_EN3: TP125.1, U17.9, U20.10
RP_IO7/MOT_L_EN4: TP164.1, U22.9, U25.10
RP_IO7/MOT_L_EN5: TP203.1, U27.9, U30.10
RP_IO8/ENC_4_A: J6.4, TP9.1, U1.11
RP_IO8/ENC_4_A1: J15.4, TP48.1, U10.11
RP_IO8/ENC_4_A2: J26.4, TP87.1, U15.11
RP_IO8/ENC_4_A3: J37.4, TP126.1, U20.11
RP_IO8/ENC_4_A4: J48.4, TP165.1, U25.11
RP_IO8/ENC_4_A5: J59.4, TP204.1, U30.11
RP_IO9/ENC_4_B: J6.5, TP10.1, U1.12
RP_IO9/ENC_4_B1: J15.5, TP49.1, U10.12
RP_IO9/ENC_4_B2: J26.5, TP88.1, U15.12
RP_IO9/ENC_4_B3: J37.5, TP127.1, U20.12
RP_IO9/ENC_4_B4: J48.5, TP166.1, U25.12
RP_IO9/ENC_4_B5: J59.5, TP205.1, U30.12
RP_IO10/MOT_4_PH: TP11.1, U1.14, U6.10
RP_IO10/MOT_4_PH1: TP50.1, U8.10, U10.14
RP_IO10/MOT_4_PH2: TP89.1, U13.10, U15.14
RP_IO10/MOT_4_PH3: TP128.1, U18.10, U20.14
RP_IO10/MOT_4_PH4: TP167.1, U23.10, U25.14
RP_IO10/MOT_4_PH5: TP206.1, U28.10, U30.14
RP_IO11/MOT_4_EN: TP12.1, U1.15, U6.9
RP_IO11/MOT_4_EN1: TP51.1, U8.9, U10.15
RP_IO11/MOT_4_EN2: TP90.1, U13.9, U15.15
RP_IO11/MOT_4_EN3: TP129.1, U18.9, U20.15
RP_IO11/MOT_4_EN4: TP168.1, U23.9, U25.15
RP_IO11/MOT_4_EN5: TP207.1, U28.9, U30.15
RP_IO12/ENC_R_A: J5.4, TP13.1, U1.16
RP_IO12/ENC_R_A1: J11.4, TP52.1, U10.16
RP_IO12/ENC_R_A2: J25.4, TP91.1, U15.16
RP_IO12/ENC_R_A3: J36.4, TP130.1, U20.16
RP_IO12/ENC_R_A4: J47.4, TP169.1, U25.16
RP_IO12/ENC_R_A5: J58.4, TP208.1, U30.16
RP_IO13/ENC_R_B: J5.5, TP14.1, U1.17
RP_IO13/ENC_R_B1: J11.5, TP53.1, U10.17
RP_IO13/ENC_R_B2: J25.5, TP92.1, U15.17
RP_IO13/ENC_R_B3: J36.5, TP131.1, U20.17
RP_IO13/ENC_R_B4: J47.5, TP170.1, U25.17
RP_IO13/ENC_R_B5: J58.5, TP209.1, U30.17
RP_IO14/MOT_R_PH: TP15.1, U1.19, U6.8
RP_IO14/MOT_R_PH1: TP54.1, U8.8, U10.19
RP_IO14/MOT_R_PH2: TP93.1, U13.8, U15.19
RP_IO14/MOT_R_PH3: TP132.1, U18.8, U20.19
RP_IO14/MOT_R_PH4: TP171.1, U23.8, U25.19
RP_IO14/MOT_R_PH5: TP210.1, U28.8, U30.19
RP_IO15/MOT_R_EN: TP16.1, U1.20, U6.7
RP_IO15/MOT_R_EN1: TP55.1, U8.7, U10.20
RP_IO15/MOT_R_EN2: TP94.1, U13.7, U15.20
RP_IO15/MOT_R_EN3: TP133.1, U18.7, U20.20
RP_IO15/MOT_R_EN4: TP172.1, U23.7, U25.20
RP_IO15/MOT_R_EN5: TP211.1, U28.7, U30.20
RP_IO16/S1_OUT: J7.3, U1.21
RP_IO16/S1_OUT1: J16.3, U10.21
RP_IO16/S1_OUT2: J27.3, U15.21
RP_IO16/S1_OUT3: J38.3, U20.21
RP_IO16/S1_OUT4: J49.3, U25.21
RP_IO16/S1_OUT5: J60.3, U30.21
RP_IO17/S2_OUT: J8.1, U1.22
RP_IO17/S2_OUT1: J17.1, U10.22
RP_IO17/S2_OUT2: J28.1, U15.22
RP_IO17/S2_OUT3: J39.1, U20.22
RP_IO17/S2_OUT4: J50.1, U25.22
RP_IO17/S2_OUT5: J61.1, U30.22
RP_IO18/SDA: J9.3, R1.1, TP17.1, U1.24, U4.14
RP_IO18/SDA1: J18.3, R22.1, TP56.1, U3.14, U10.24
RP_IO18/SDA2: J29.3, R42.1, TP95.1, U11.14, U15.24
RP_IO18/SDA3: J40.3, R62.1, TP134.1, U16.14, U20.24
RP_IO18/SDA4: J51.3, R82.1, TP173.1, U21.14, U25.24
RP_IO18/SDA5: J62.3, R102.1, TP212.1, U26.14, U30.24
RP_IO19/SCL: J9.4, R2.2, TP18.1, U1.25, U4.13
RP_IO19/SCL1: J18.4, R23.2, TP57.1, U3.13, U10.25
RP_IO19/SCL2: J29.4, R43.2, TP96.1, U11.13, U15.25
RP_IO19/SCL3: J40.4, R63.2, TP135.1, U16.13, U20.25
RP_IO19/SCL4: J51.4, R83.2, TP174.1, U21.13, U25.25
RP_IO19/SCL5: J62.4, R103.2, TP213.1, U26.13, U30.25
RP_IO20/RANGE_TRIG: J12.3, TP19.1, U1.26
RP_IO20/RANGE_TRIG1: J19.3, TP58.1, U10.26
RP_IO20/RANGE_TRIG2: J30.3, TP97.1, U15.26
RP_IO20/RANGE_TRIG3: J41.3, TP136.1, U20.26
RP_IO20/RANGE_TRIG4: J52.3, TP175.1, U25.26
RP_IO20/RANGE_TRIG5: J63.3, TP214.1, U30.26
RP_IO21/RANGE_ECHO: J12.4, TP20.1, U1.27
RP_IO21/RANGE_ECHO1: J19.4, TP59.1, U10.27
RP_IO21/RANGE_ECHO2: J30.4, TP98.1, U15.27
RP_IO21/RANGE_ECHO3: J41.4, TP137.1, U20.27
RP_IO21/RANGE_ECHO4: J52.4, TP176.1, U25.27
RP_IO21/RANGE_ECHO5: J63.4, TP215.1, U30.27
RP_IO22/USER_BTN: J13.3, TP21.1, U1.29, USER_BTN.2
RP_IO22/USER_BTN1: J20.3, TP60.1, U10.29, USER_BTN1.2
RP_IO22/USER_BTN2: J31.3, TP99.1, U15.29, USER_BTN2.2
RP_IO22/USER_BTN3: J42.3, TP138.1, U20.29, USER_BTN3.2
RP_IO22/USER_BTN4: J53.3, TP177.1, U25.29, USER_BTN4.2
RP_IO22/USER_BTN5: J64.3, TP216.1, U30.29, USER_BTN5.2
RP_IO26/LINE_L: J14.3, TP22.1, U1.31
RP_IO26/LINE_L1: J21.3, TP61.1, U10.31
RP_IO26/LINE_L2: J32.3, TP100.1, U15.31
RP_IO26/LINE_L3: J43.3, TP139.1, U20.31
RP_IO26/LINE_L4: J54.3, TP178.1, U25.31
RP_IO26/LINE_L5: J65.3, TP217.1, U30.31
RP_IO27/LINE_R: J14.4, TP23.1, U1.32
RP_IO27/LINE_R1: J21.4, TP62.1, U10.32
RP_IO27/LINE_R2: J32.4, TP101.1, U15.32
RP_IO27/LINE_R3: J43.4, TP140.1, U20.32
RP_IO27/LINE_R4: J54.4, TP179.1, U25.32
RP_IO27/LINE_R5: J65.4, TP218.1, U30.32
RP_IO28/VIN_MEAS: J13.4, TP24.1, U1.34, VIN_MEAS.1
RP_IO28/VIN_MEAS1: J20.4, TP63.1, U10.34, VIN_MEAS1.1
RP_IO28/VIN_MEAS2: J31.4, TP102.1, U15.34, VIN_MEAS2.1
RP_IO28/VIN_MEAS3: J42.4, TP141.1, U20.34, VIN_MEAS3.1
RP_IO28/VIN_MEAS4: J53.4, TP180.1, U25.34, VIN_MEAS4.1
RP_IO28/VIN_MEAS5: J64.4, TP219.1, U30.34, VIN_MEAS5.1
SW: C10.2, L1.P$1, U2.P$7, U2.P$9
SW1: C25.2, L2.P$1, U9.P$7, U9.P$9
SW2: C40.2, L3.P$1, U14.P$7, U14.P$9
SW3: C55.2, L4.P$1, U19.P$7, U19.P$9
SW4: C70.2, L5.P$1, U24.P$7, U24.P$9
SW5: C85.2, L6.P$1, U29.P$7, U29.P$9
VIN: C3.+, C5.+, C7.1, C8.1, C9.1, F1.2, R16.2, U2.P$1, U5.1, U6.1
VIN1: C19.+, C20.+, C22.1, C23.1, C24.1, F2.2, R35.2, U7.1, U8.1, U9.P$1
VIN2: C34.+, C35.+, C37.1, C38.1, C39.1, F3.2, R55.2, U12.1, U13.1, U14.P$1
VIN3: C49.+, C50.+, C52.1, C53.1, C54.1, F4.2, R75.2, U17.1, U18.1, U19.P$1
VIN4: C64.+, C65.+, C67.1, C68.1, C69.1, F5.2, R95.2, U22.1, U23.1, U24.P$1
VIN5: C79.+, C80.+, C82.1, C83.1, C84.1, F6.2, R115.2, U27.1, U28.1, U29.P$1
V_BATT: J1.PWR, Q1.1, Q3.3, TP34.1
V_BATT1: J22.PWR, Q8.3, Q10.1, TP76.1
V_BATT2: J33.PWR, Q15.3, Q17.1, TP115.1
V_BATT3: J44.PWR, Q22.3, Q24.1, TP154.1
V_BATT4: J55.PWR, Q29.3, Q31.1, TP193.1
V_BATT5: J66.PWR, Q36.3, Q38.1, TP232.1
V_POW: Q1.4, Q2.4, Q3.2, Q4.2, Q6.2, R12.2
V_POW1: Q8.2, Q9.2, Q10.4, Q11.4, Q12.2, R31.2
V_POW2: Q15.2, Q16.2, Q17.4, Q18.4, Q19.2, R51.2
V_POW3: Q22.2, Q23.2, Q24.4, Q25.4, Q26.2, R71.2
V_POW4: Q29.2, Q30.2, Q31.4, Q32.4, Q33.2, R91.2
V_POW5: Q36.2, Q37.2, Q38.4, Q39.4, Q40.2, R111.2
V_SYS: Q5.2, Q7.4, U1.39
V_SYS1: Q13.2, Q14.4, U10.39
V_SYS2: Q20.2, Q21.4, U15.39
V_SYS3: Q27.2, Q28.4, U20.39
V_SYS4: Q34.2, Q35.4, U25.39
V_SYS5: Q41.2, Q42.4, U30.39
V_USB: Q2.1, Q4.3, R18.2, R19.2
V_USB1: Q9.3, Q11.1, R38.2, R39.2
V_USB2: Q16.3, Q18.1, R58.2, R59.2
V_USB3: Q23.3, Q25.1, R78.2, R79.2
V_USB4: Q30.3, Q32.1, R98.2, R99.2
V_USB5: Q37.3, Q39.1, R118.2, R119.2
